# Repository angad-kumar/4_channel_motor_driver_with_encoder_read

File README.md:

#3D view

# Schematics

#Layout

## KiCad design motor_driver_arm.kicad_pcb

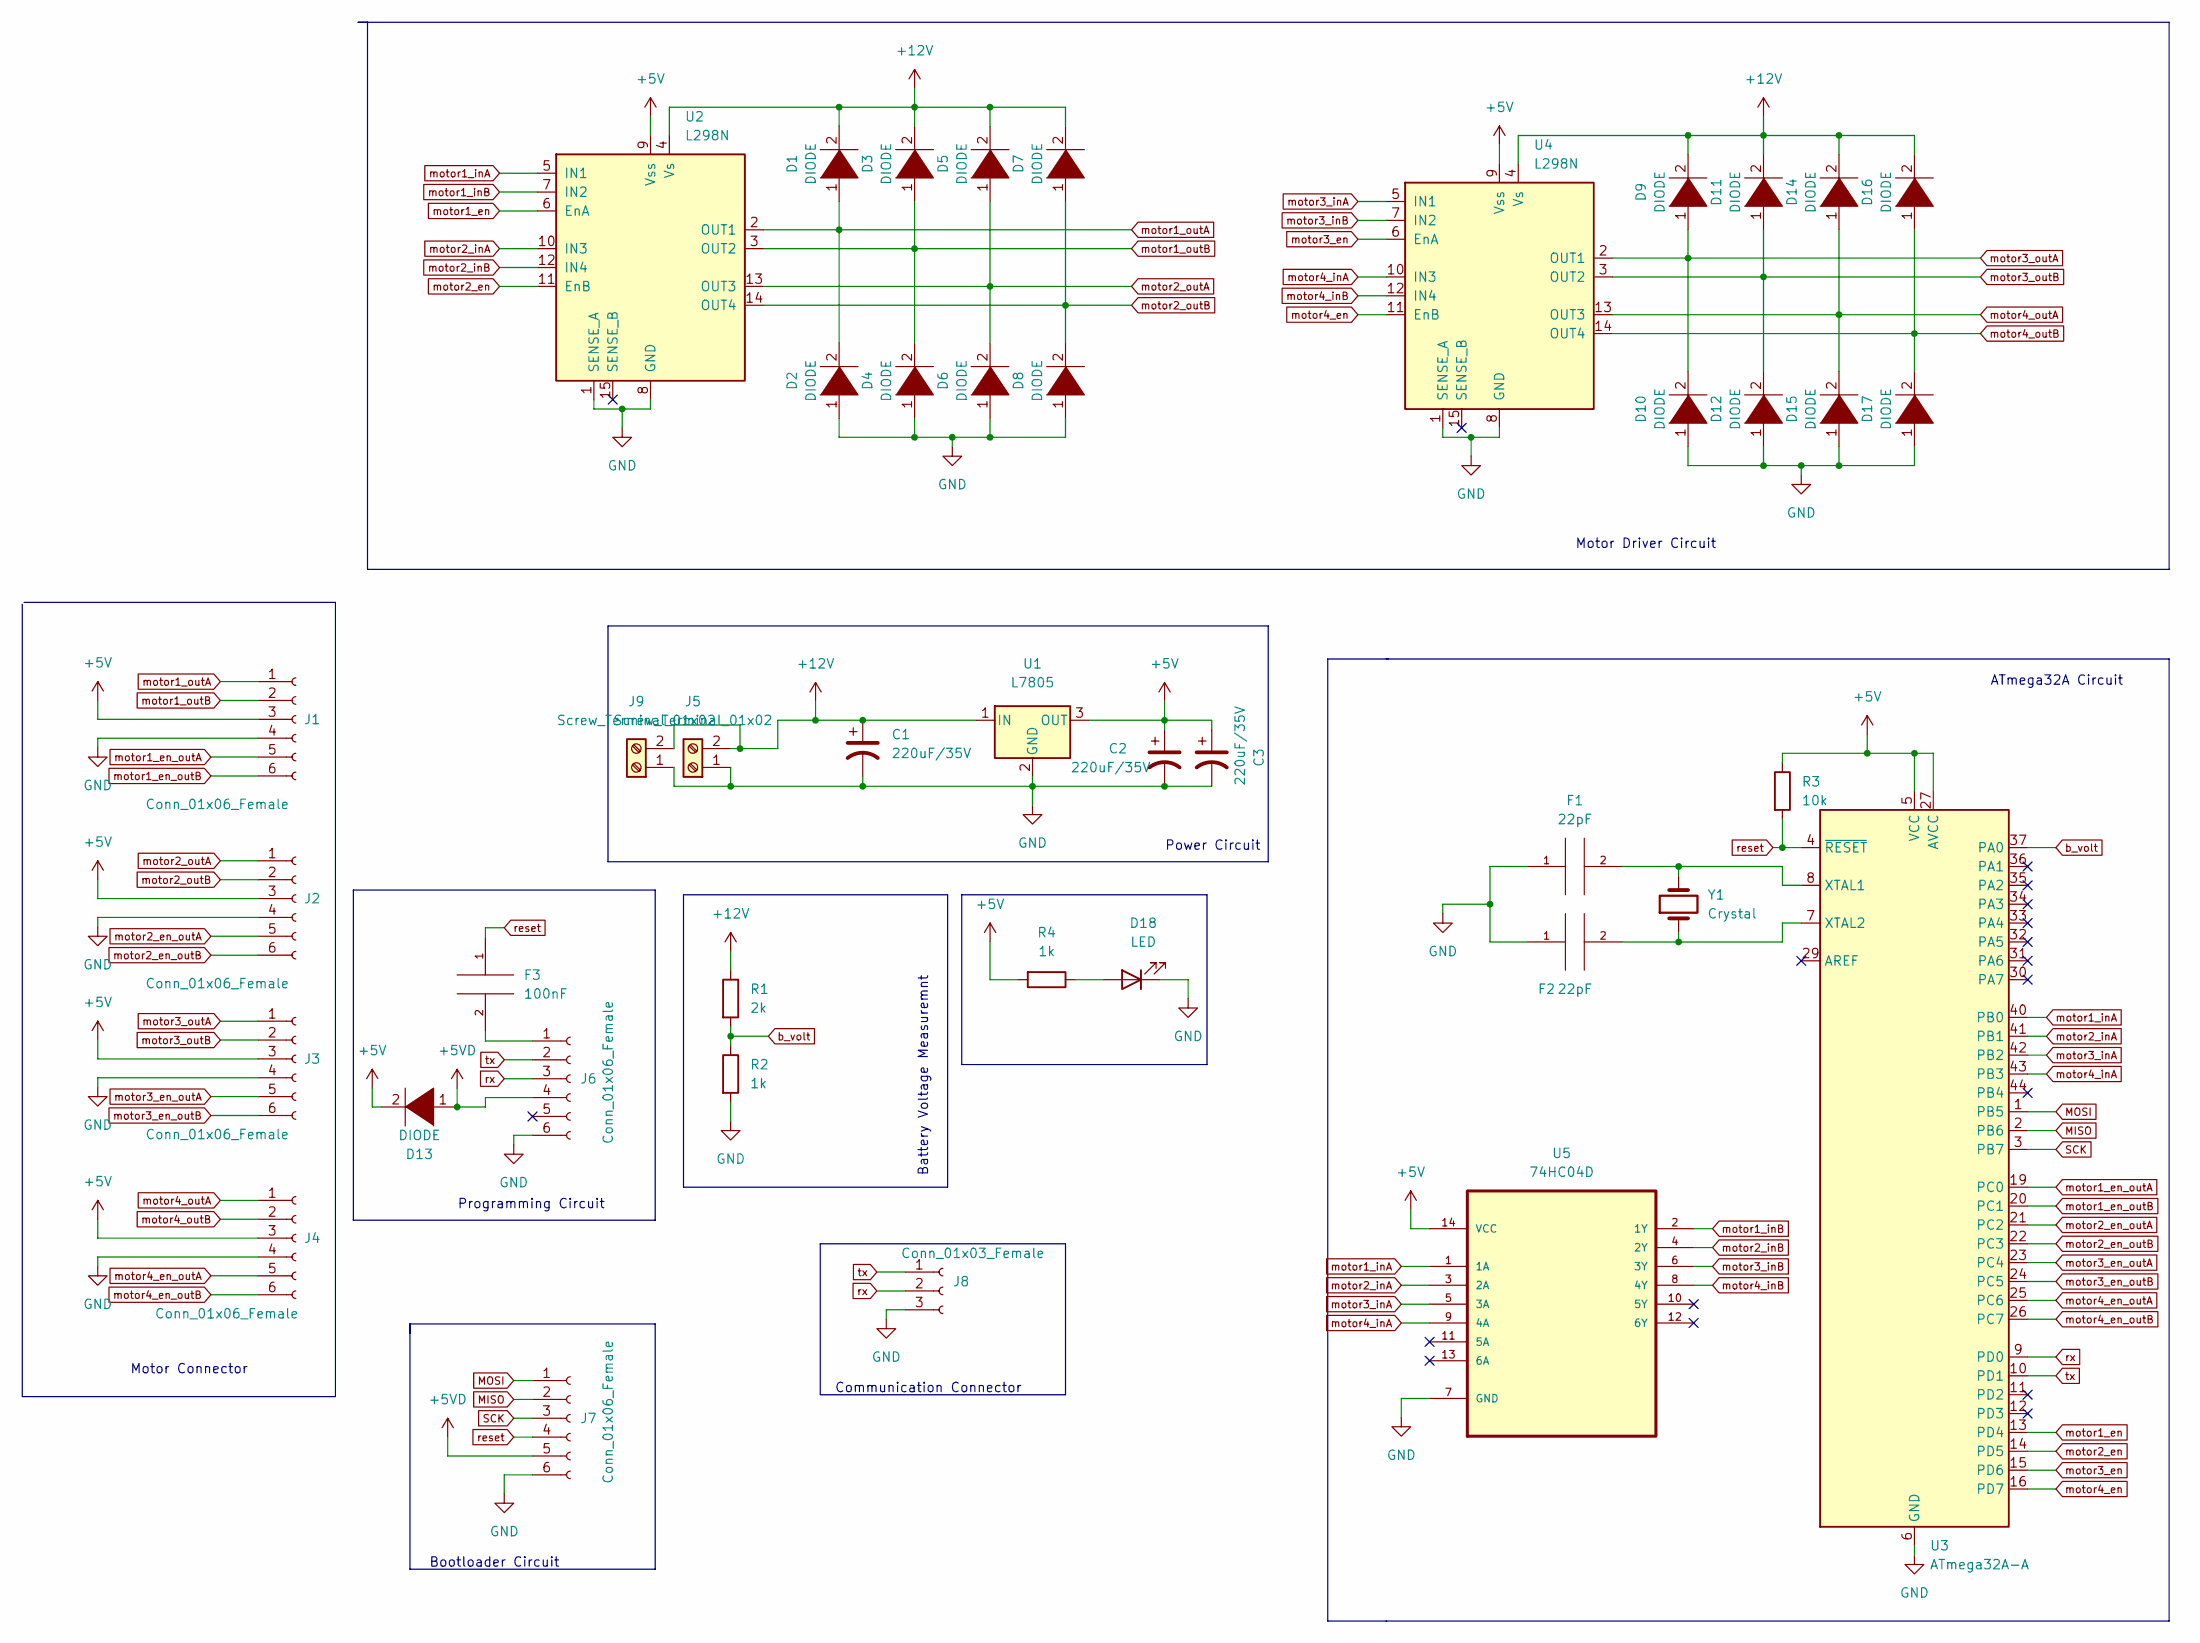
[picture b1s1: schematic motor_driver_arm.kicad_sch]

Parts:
C1, C2, C3: 220uF/35V; CP_Elec_8x10.5
D1, D2, D3, D4, D5, D6, D7, D8, D9, D10, D11, D12, D13, D14, D15, D16, D17: DIODE; D_SMA
D18: LED; LED_0805_2012Metric
F1, F2: 22pF; C_0805_2012Metric
F3: 100nF; C_0805_2012Metric
J1, J2, J3, J4: Conn_01x06_Female; JST_XH_B6B-XH-AM_1x06_P2.50mm_Vertical
J5: Screw_Terminal_01x02; AMASS_XT60-F_1x02_P7.20mm_Vertical
J6, J7: Conn_01x06_Female; PinHeader_1x06_P2.54mm_Vertical
J8: Conn_01x03_Female; JST_XH_B3B-XH-A_1x03_P2.50mm_Vertical
J9: Screw_Terminal_01x02; TerminalBlock_bornier-2_P5.08mm
R1: 2k; R_0805_2012Metric
R2, R4: 1k; R_0805_2012Metric
R3: 10k; R_0805_2012Metric
U1: L7805; TO-252-2
U2, U4: L298N; TO-220-15_P2.54x2.54mm_StaggerOdd_Lead4.58mm_Vertical
U3: ATmega32A-A; TQFP-44_10x10mm_P0.8mm
U5: 74HC04D; SOIC127P600X175-14N; MPN 74HC04D
Y1: Crystal; Crystal_SMD_HC49-SD

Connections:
+5V: C2.1, C3.1, D13.2 (A), J1.3, J2.3, J3.3, J4.3, R3.1, R4.2, U1.3 (OUT), U2.9 (Vss), U3.5 (VCC), U3.17 (VCC), U3.27 (AVCC), U3.38 (VCC), U4.9 (Vss), U5.14 (VCC)
+5VD: D13.1 (K), J6.4, J7.5
+12V: C1.1, D1.2 (A), D3.2 (A), D5.2 (A), D7.2 (A), D9.2 (A), D11.2 (A), D14.2 (A), D16.2 (A), J5.2, J9.2, R1.1, U1.1 (IN), U2.4 (Vs), U4.4 (Vs)
GND: C1.2, C2.2, C3.2, D2.1 (K), D4.1 (K), D6.1 (K), D8.1 (K), D10.1 (K), D12.1 (K), D15.1 (K), D17.1 (K), D18.1 (K), F1.1, F2.1, J1.4, J2.4, J3.4, J4.4, J5.1, J6.6, J7.6, J8.3, J9.1, R2.2, U1.2 (GND), U2.1 (SENSE_A), U2.8 (GND), U3.6 (GND), U3.18 (GND), U3.28 (GND), U3.39 (GND), U4.1 (SENSE_A), U4.8 (GND), U5.7 (GND)
MISO: J7.2, U3.2 (PB6)
MOSI: J7.1, U3.1 (PB5)
unnamed: D18.2 (A), R4.1
unnamed: F1.2, U3.8 (XTAL1), Y1.2
unnamed: F2.2, U3.7 (XTAL2), Y1.1
unnamed: F3.2, J6.1
SCK: J7.3, U3.3 (PB7)
b_volt: R1.2, R2.1, U3.37 (PA0)
motor1_en: U2.6 (EnA), U3.13 (PD4)
motor1_en_outA: J1.5, U3.19 (PC0)
motor1_en_outB: J1.6, U3.20 (PC1)
motor1_inA: U2.5 (IN1), U3.40 (PB0), U5.1 (1A)
motor1_inB: U2.7 (IN2), U5.2 (1Y)
motor1_outA: D1.1 (K), D2.2 (A), J1.1, U2.2 (OUT1)
motor1_outB: D3.1 (K), D4.2 (A), J1.2, U2.3 (OUT2)
motor2_en: U2.11 (EnB), U3.14 (PD5)
motor2_en_outA: J2.5, U3.21 (PC2)
motor2_en_outB: J2.6, U3.22 (PC3)
motor2_inA: U2.10 (IN3), U3.41 (PB1), U5.3 (2A)
motor2_inB: U2.12 (IN4), U5.4 (2Y)
motor2_outA: D5.1 (K), D6.2 (A), J2.1, U2.13 (OUT3)
motor2_outB: D7.1 (K), D8.2 (A), J2.2, U2.14 (OUT4)
motor3_en: U3.15 (PD6), U4.6 (EnA)
motor3_en_outA: J3.5, U3.23 (PC4)
motor3_en_outB: J3.6, U3.24 (PC5)
motor3_inA: U3.42 (PB2), U4.5 (IN1), U5.5 (3A)
motor3_inB: U4.7 (IN2), U5.6 (3Y)
motor3_outA: D9.1 (K), D10.2 (A), J3.1, U4.2 (OUT1)
motor3_outB: D11.1 (K), D12.2 (A), J3.2, U4.3 (OUT2)
motor4_en: U3.16 (PD7), U4.11 (EnB)
motor4_en_outA: J4.5, U3.25 (PC6)
motor4_en_outB: J4.6, U3.26 (PC7)
motor4_inA: U3.43 (PB3), U4.10 (IN3), U5.9 (4A)
motor4_inB: U4.12 (IN4), U5.8 (4Y)
motor4_outA: D14.1 (K), D15.2 (A), J4.1, U4.13 (OUT3)
motor4_outB: D16.1 (K), D17.2 (A), J4.2, U4.14 (OUT4)
reset: F3.1, J7.4, R3.2, U3.4 (~RESET)
rx: J6.3, J8.2, U3.9 (PD0)
tx: J6.2, J8.1, U3.10 (PD1)

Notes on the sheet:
Battery Voltage Measuremnt
Bootloader Circuit
Motor Driver Circuit
Communication Connector
ATmega32A Circuit
Programming Circuit
Motor Connector
Power Circuit

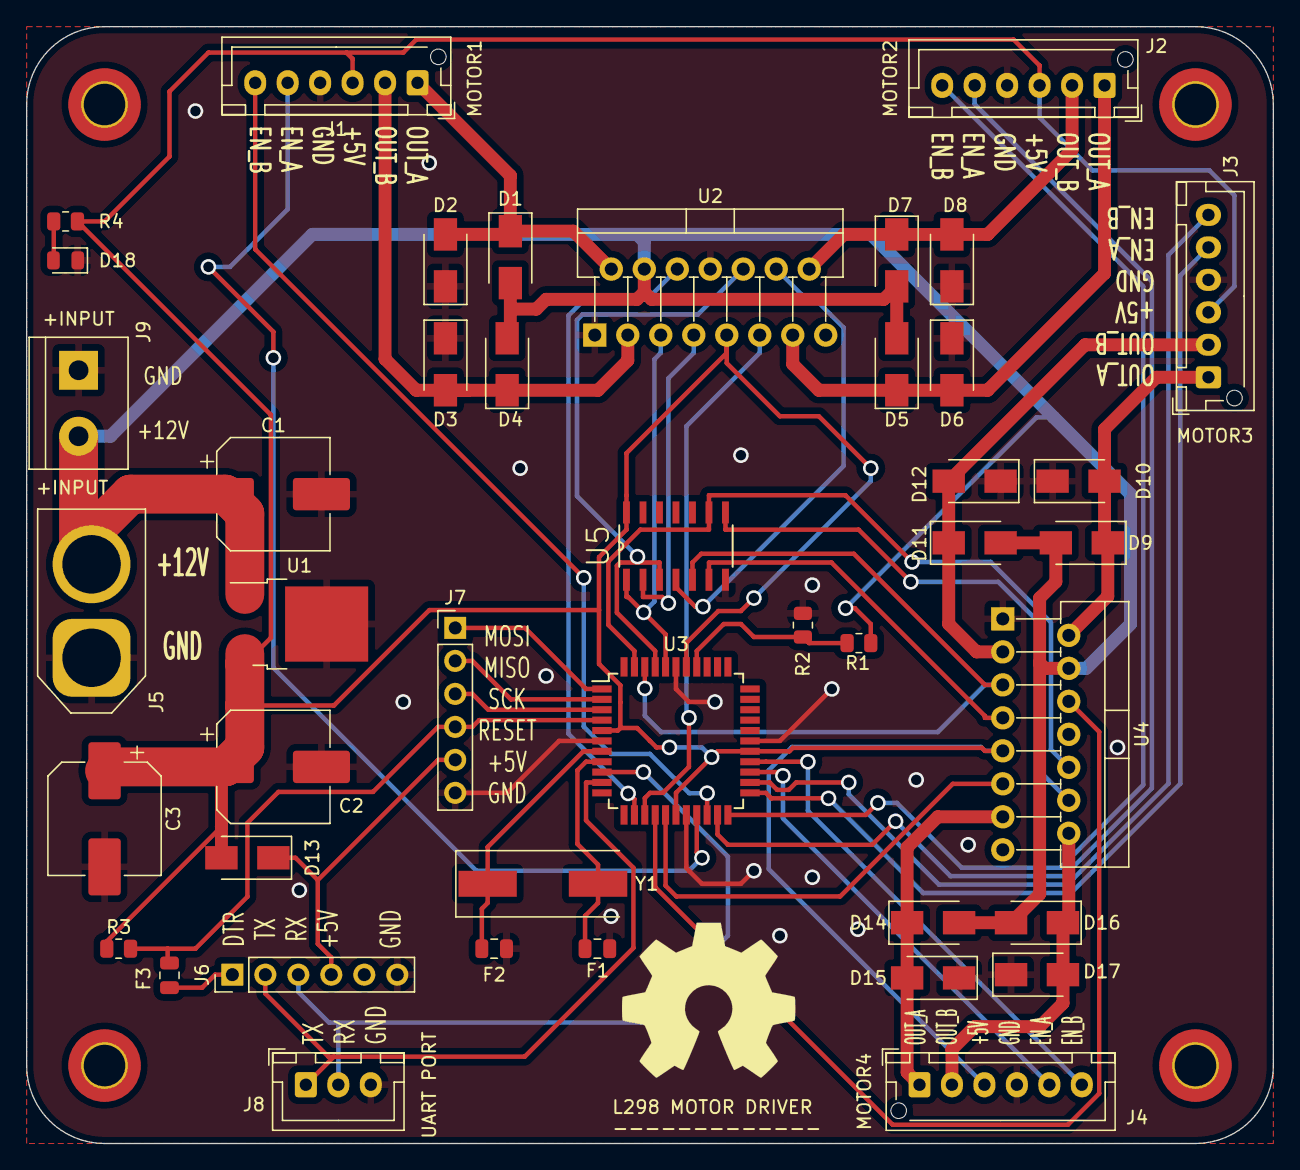
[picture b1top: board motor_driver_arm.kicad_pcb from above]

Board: 2 copper layers, 96.0 x 86.0 mm, 47 parts (0 on the bottom side), 43 nets.

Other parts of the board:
m3_1, m3_2, m3_3, m3_4: MountingHole_3.2mm_M3_DIN965_Pad_TopBottom
